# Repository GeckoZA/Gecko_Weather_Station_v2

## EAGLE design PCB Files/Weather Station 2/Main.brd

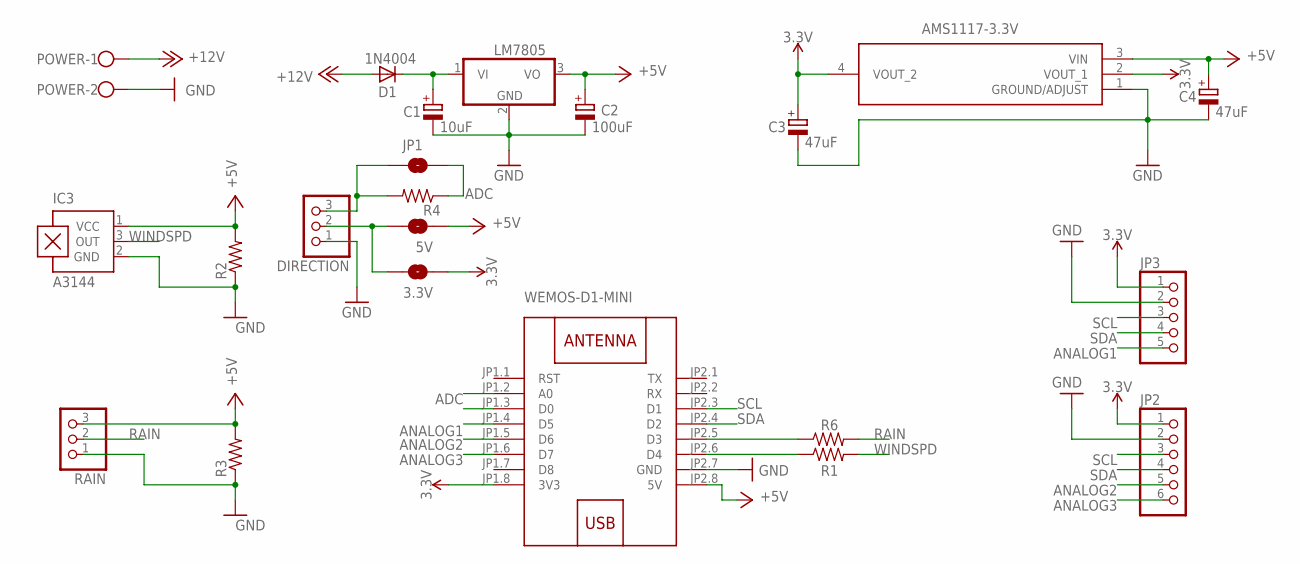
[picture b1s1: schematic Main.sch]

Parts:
3.3V, 5V: JUMPER-SMT_2_NO_NO-SILK; SMT-JUMPER_2_NO_NO-SILK
C1: 10uF; E2,5-5
C2: 100uF; E2,5-5
C3, C4: 47uF; E2,5-5
D1: 1N4004; DO41-10
DIRECTION: PINHD-1X3/90; 1X03/90
IC1: LM7805; TO220H
IC2: AMS1117-3.3V; SOT229P700X180-4N
IC3: A3144; SIP3-UA
JP1: JUMPER-SMT_2_NO_NO-SILK; SMT-JUMPER_2_NO_NO-SILK
JP2: PINHD-1X6/90; 1X06/90
JP3: PINHD-1X5/90; 1X05/90
POWER: W237-102
R1, R2, R3, R4, R6: R-US_0207/10; 0207/10
RAIN: PINHD-1X3/90; 1X03/90
U$1: WEMOS-D1-MINI

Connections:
3.3V: 3.3V.1, C3.+, IC2.2 (VOUT_1), IC2.4 (VOUT_2), JP2.1, JP3.1, U$1.JP1.8 (3V3)
+5V: 5V.1, C2.+, C4.+, IC1.3 (VO), IC2.3 (VIN), IC3.1 (VCC), R2.2, R3.2, RAIN.3, U$1.JP2.8 (5V)
+12V: D1.A, POWER.1
ADC: JP1.2, R4.1, U$1.JP1.2 (A0)
ANALOG1: JP3.5, U$1.JP1.4 (D5)
ANALOG2: JP2.5, U$1.JP1.5 (D6)
ANALOG3: JP2.6, U$1.JP1.6 (D7)
GND: C1.-, C2.-, C3.-, C4.-, DIRECTION.1, IC1.2 (GND), IC2.1 (GROUND/ADJUST), IC3.2 (GND), JP2.2, JP3.2, POWER.2, R2.1, R3.1, RAIN.1, U$1.JP2.7 (GND)
unnamed: C1.+, D1.C, IC1.1 (VI)
unnamed: R1.1, U$1.JP2.6 (D4)
unnamed: R6.1, U$1.JP2.5 (D3)
unnamed: DIRECTION.3, JP1.1, R4.2
unnamed: 3.3V.2, 5V.2, DIRECTION.2
RAIN: R6.2, RAIN.2
SCL: JP2.3, JP3.3, U$1.JP2.3 (D1)
SDA: JP2.4, JP3.4, U$1.JP2.4 (D2)
WINDSPD: IC3.3 (OUT), R1.2

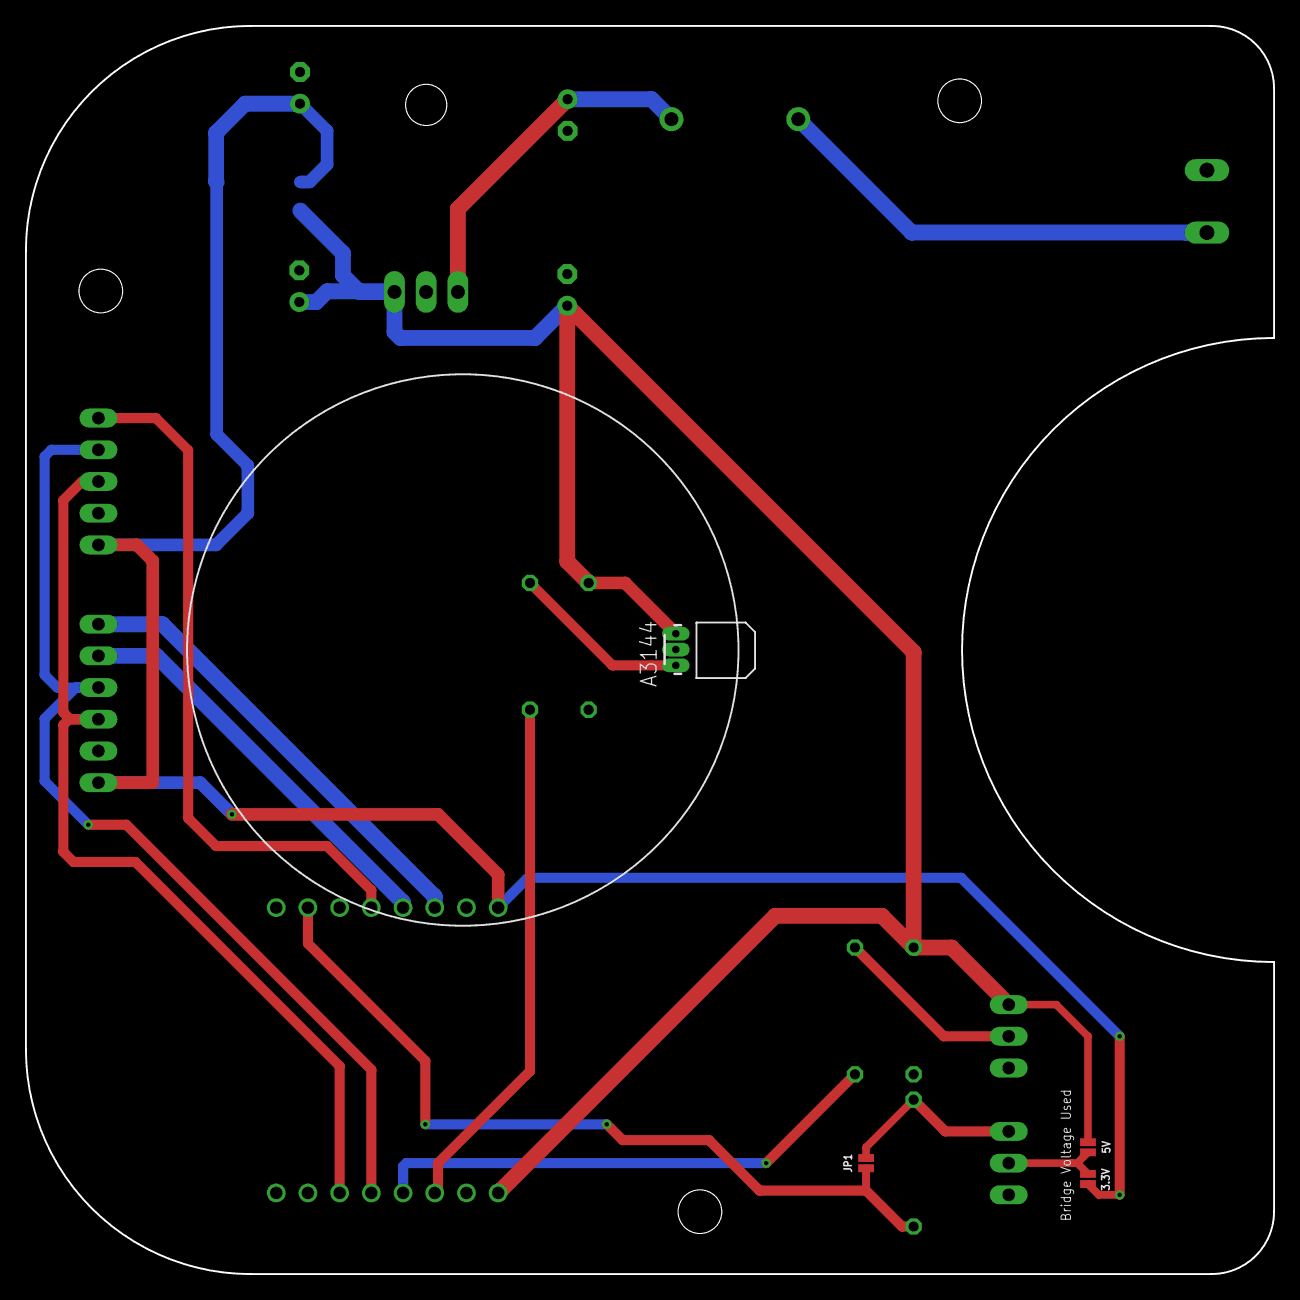
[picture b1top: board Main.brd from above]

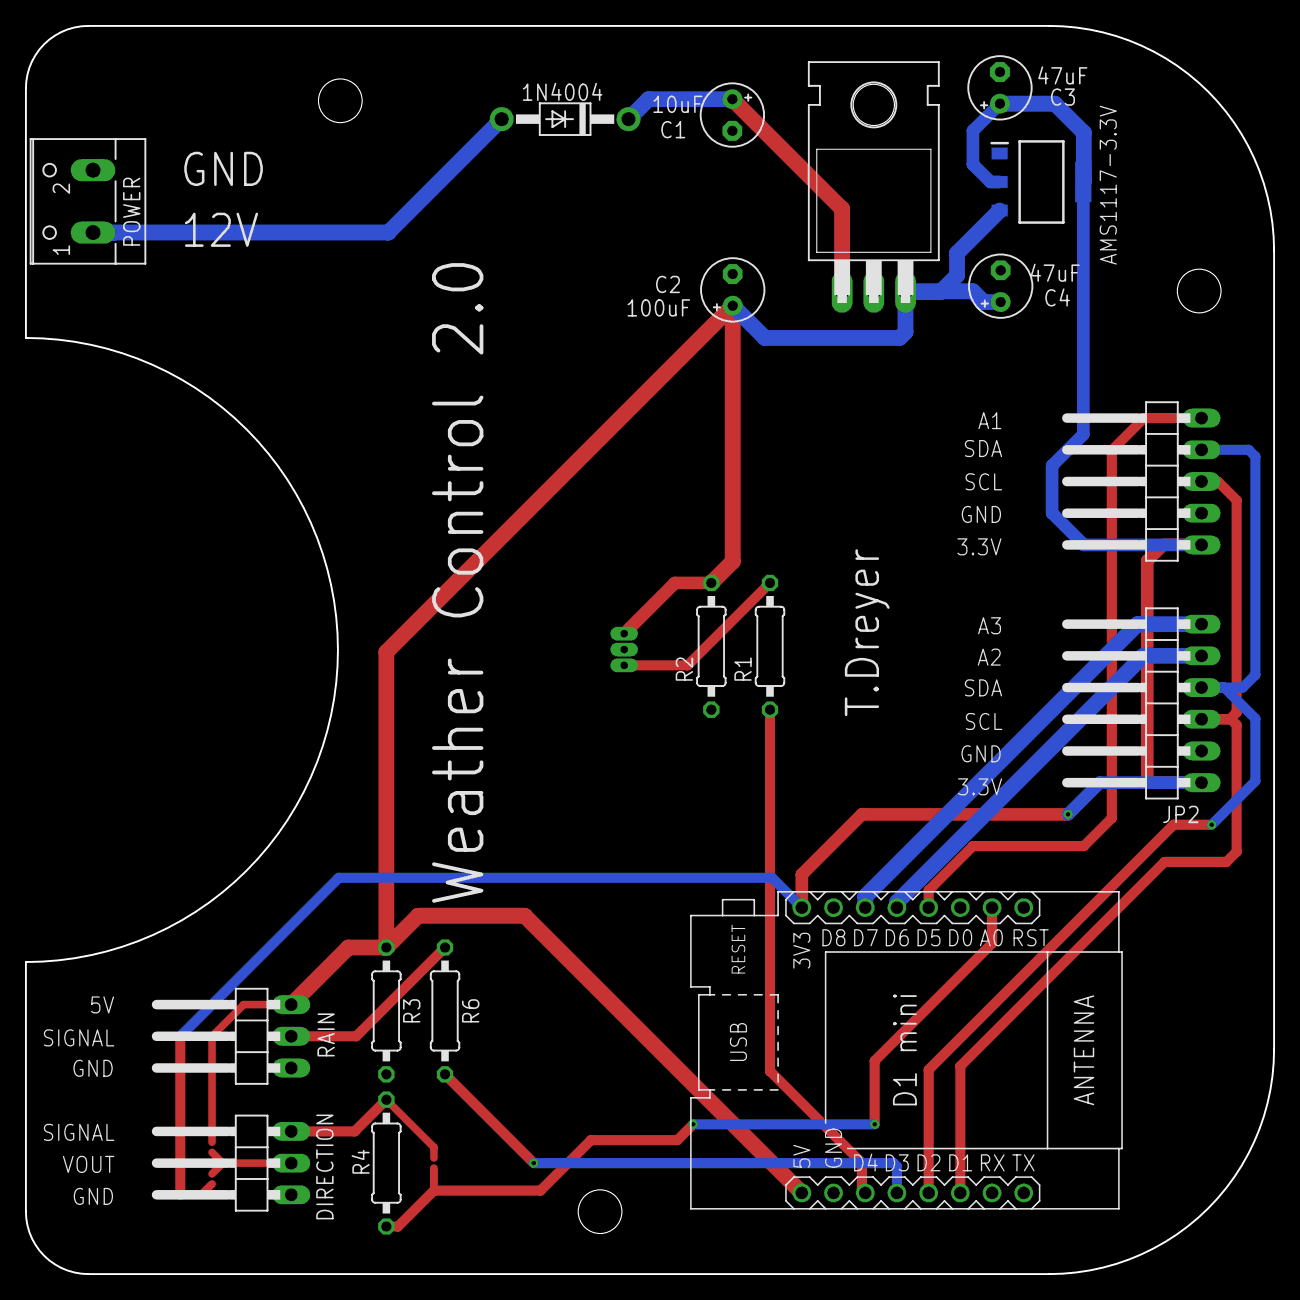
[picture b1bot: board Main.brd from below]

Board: 2 copper layers, 100.0 x 100.0 mm, 22 parts (18 on the bottom side), 17 nets.

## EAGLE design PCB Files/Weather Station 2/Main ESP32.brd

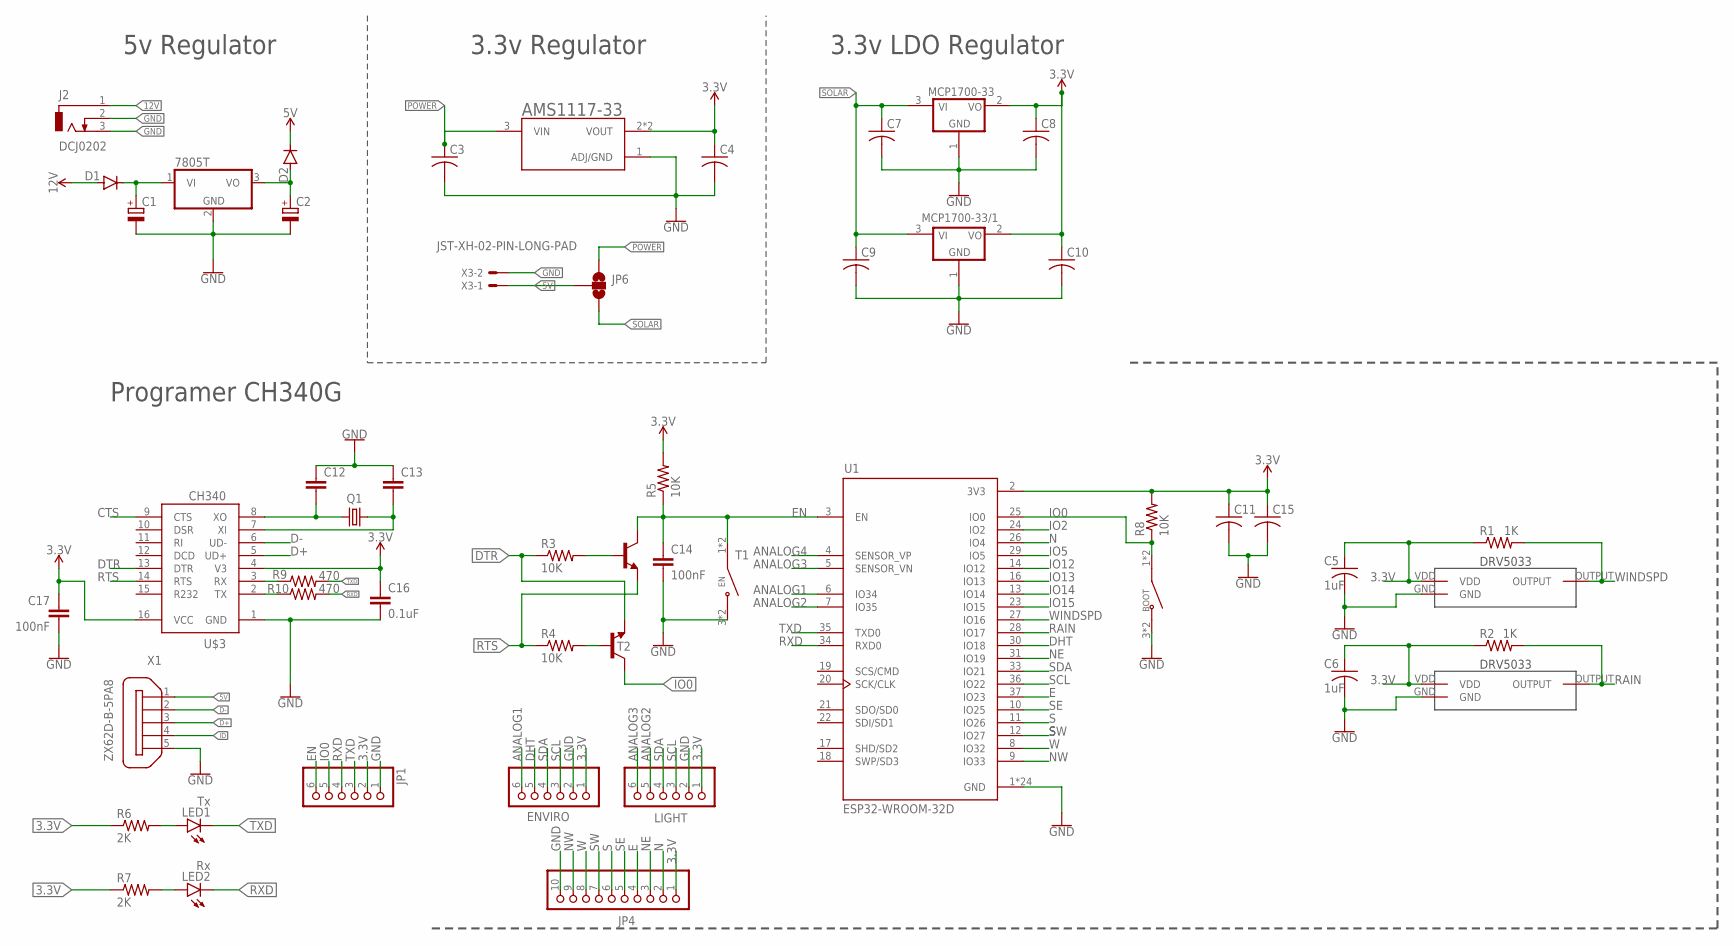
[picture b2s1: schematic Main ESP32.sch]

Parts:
AMS1117-33: AMS1117-5.0; SOT229P700X180-4N
BOOT: 2-1437565-9; SW_2-1437565-9
C1, C2: CPOL-EUE2.5-5; E2,5-5
C3, C4, C7, C8, C9, C10, C11, C15: C-USC1206K; C1206K
C5, C6: 1uF; C1206K
C12, C13: C-EUC1206K; C1206K
C14, C17: 100nF; C1206K
C16: 0.1uF; C1206K
D1, D2: 1N4148DO35-10; DO35-10
EN: 2-1437565-9; SW_2-1437565-9
ENVIRO: PINHD-1X6/90; 1X06/90
IC1: 7805T; TO220H
J2: DCJ0202
JP1: PINHD-1X6; 1X06
JP4: PINHD-1X10/90; 1X10/90
JP6: JUMPER-SMT_3_NO_SILK; SMT-JUMPER_3_NO_SILK
LED1: Tx; CHIPLED_1206
LED2: Rx; CHIPLED_1206
LIGHT: Light; 1X06/90
MCP1700-33, MCP1700-33/1: MCP1703-3302E/CB; SOT23A_MICROCHIP_CB
Q1: CRYSTALHC49S; HC49/S
R1, R2: 1K; R1206
R3, R4, R5, R8: 10K; R1206
R6, R7: 2K; R1206
R9, R10: 470; R1206
T1, T2: BC847; SOT23
U1: ESP32-WROOM-32D; MODULE_ESP32-WROOM-32D
U$1, U$2: DRV5033
U$3: CH340; SOIC16
X1: ZX62D-B-5PA8
X3: JST-XH-02-PIN-LONG-PAD; JST-XH-02-PACKAGE-LONG-PAD

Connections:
3.3V: AMS1117-33.2 (VOUT), AMS1117-33.4 (VOUT), C4.1, C5.1, C6.1, C8.1, C10.1, C11.1, C15.1, C16.1, C17.1, ENVIRO.1, JP1.2, JP4.1, LIGHT.1, MCP1700-33.2 (VO), MCP1700-33/1.2 (VO), R1.1, R2.1, R5.2, R6.1, R7.1, R8.2, U1.2 (3V3), U$1.VDD, U$2.VDD, U$3.4 (V3), U$3.16 (VCC)
5V: D2.C, JP6.2, X1.1, X3.1
12V: D1.A, J2.1
ANALOG1: ENVIRO.6, U1.6 (IO34)
ANALOG2: LIGHT.5, U1.7 (IO35)
ANALOG3: LIGHT.6, U1.5 (SENSOR_VN)
ANALOG4: U1.4 (SENSOR_VP)
CTS: U$3.9 (CTS)
D+: U$3.5 (UD+), X1.3
D-: U$3.6 (UD-), X1.2
DHT: ENVIRO.5, U1.30 (IO18)
DTR: R3.1, T2.2 (E), U$3.13 (DTR)
E: JP4.4, U1.37 (IO23)
EN: C14.1, EN.1 (COM), EN.2 (COM), JP1.6, R5.1, T1.3 (C), U1.3 (EN)
GND: AMS1117-33.1 (ADJ/GND), BOOT.3 (NO), BOOT.4 (NO), C1.-, C2.-, C3.2, C4.2, C5.2, C6.2, C7.2, C8.2, C9.2, C10.2, C11.2, C12.1, C13.1, C14.2, C15.2, C16.2, C17.2, EN.3 (NO), EN.4 (NO), ENVIRO.2, IC1.2 (GND), J2.2, J2.3, JP1.1, JP4.10, LIGHT.2, MCP1700-33.1 (GND), MCP1700-33/1.1 (GND), U1.1 (GND), U1.15 (GND), U1.38 (GND), U1.39_1 (GND), U1.39_2 (GND), U1.39_3 (GND), U1.39_4 (GND), U1.39_5 (GND), U1.39_6 (GND), U1.39_7 (GND), U1.39_8 (GND), U1.39_9 (GND), U1.39_10 (GND), U1.39_11 (GND), U1.39_12 (GND), U1.39_13 (GND), U1.39_14 (GND), U1.39_15 (GND), U1.39_16 (GND), U1.39_17 (GND), U1.39_18 (GND), U1.39_19 (GND), U1.39_20 (GND), U1.39_21 (GND), U$1.GND, U$2.GND, U$3.1 (GND), X1.5, X3.2
ID: X1.4
IO0: BOOT.1 (COM), BOOT.2 (COM), JP1.5, R8.1, T2.3 (C), U1.25 (IO0)
IO2: U1.24 (IO2)
IO5: U1.29 (IO5)
IO12: U1.14 (IO12)
IO13: U1.16 (IO13)
IO14: U1.13 (IO14)
IO15: U1.23 (IO15)
N: JP4.2, U1.26 (IO4)
unnamed: C1.+, D1.C, IC1.1 (VI)
unnamed: C2.+, D2.A, IC1.3 (VO)
unnamed: C12.2, Q1.2, U$3.8 (XO)
unnamed: C13.2, Q1.1, U$3.7 (XI)
unnamed: LED1.A, R6.2
unnamed: LED2.A, R7.2
unnamed: R9.1, U$3.3 (RX)
unnamed: R3.2, T1.1 (B)
unnamed: R10.1, U$3.2 (TX)
unnamed: R4.2, T2.1 (B)
NE: JP4.3, U1.31 (IO19)
NW: JP4.9, U1.9 (IO33)
POWER: AMS1117-33.3 (VIN), C3.1, JP6.1
RAIN: R2.2, U1.28 (IO17), U$1.OUTPUT
RTS: R4.1, T1.2 (E), U$3.14 (RTS)
RXD: JP1.4, LED2.C, R10.2, U1.34 (RXD0)
S: JP4.6, U1.11 (IO26)
SCL: ENVIRO.3, LIGHT.3, U1.36 (IO22)
SDA: ENVIRO.4, LIGHT.4, U1.33 (IO21)
SE: JP4.5, U1.10 (IO25)
SOLAR: C7.1, C9.1, JP6.3, MCP1700-33.3 (VI), MCP1700-33/1.3 (VI)
SW: JP4.7, U1.12 (IO27)
TXD: JP1.3, LED1.C, R9.2, U1.35 (TXD0)
W: JP4.8, U1.8 (IO32)
WINDSPD: R1.2, U1.27 (IO16), U$2.OUTPUT

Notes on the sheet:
3.3v Regulator
5v Regulator
3.3v LDO Regulator
Programer CH340G

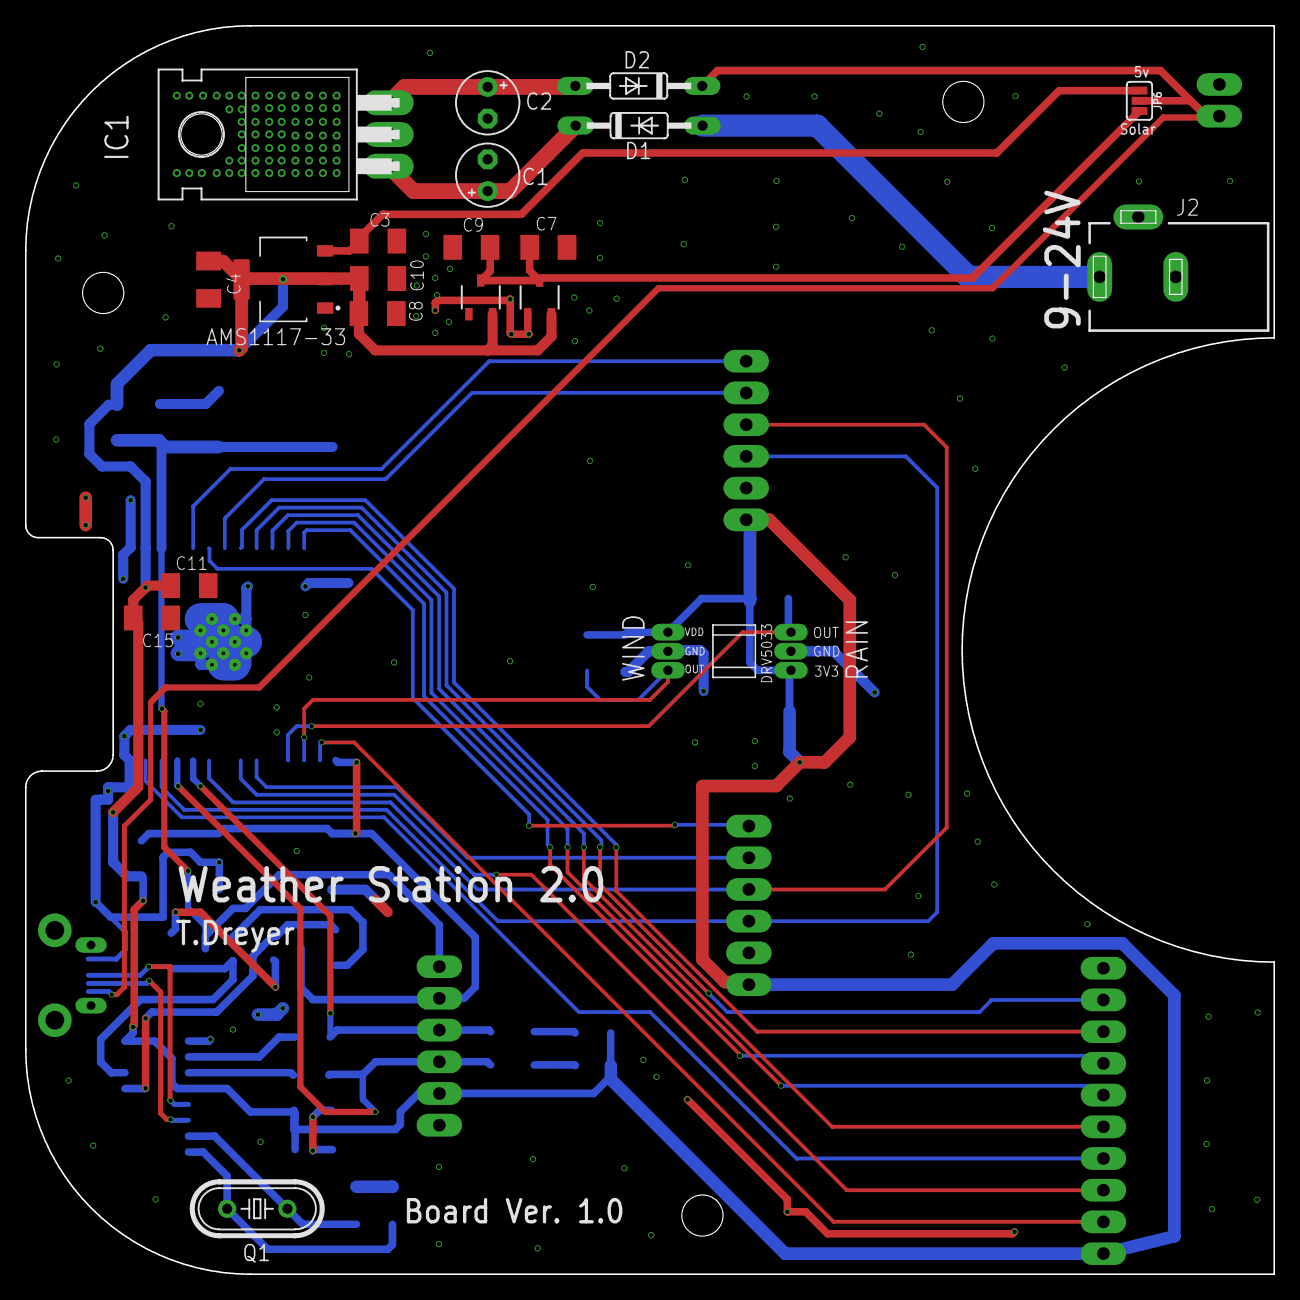
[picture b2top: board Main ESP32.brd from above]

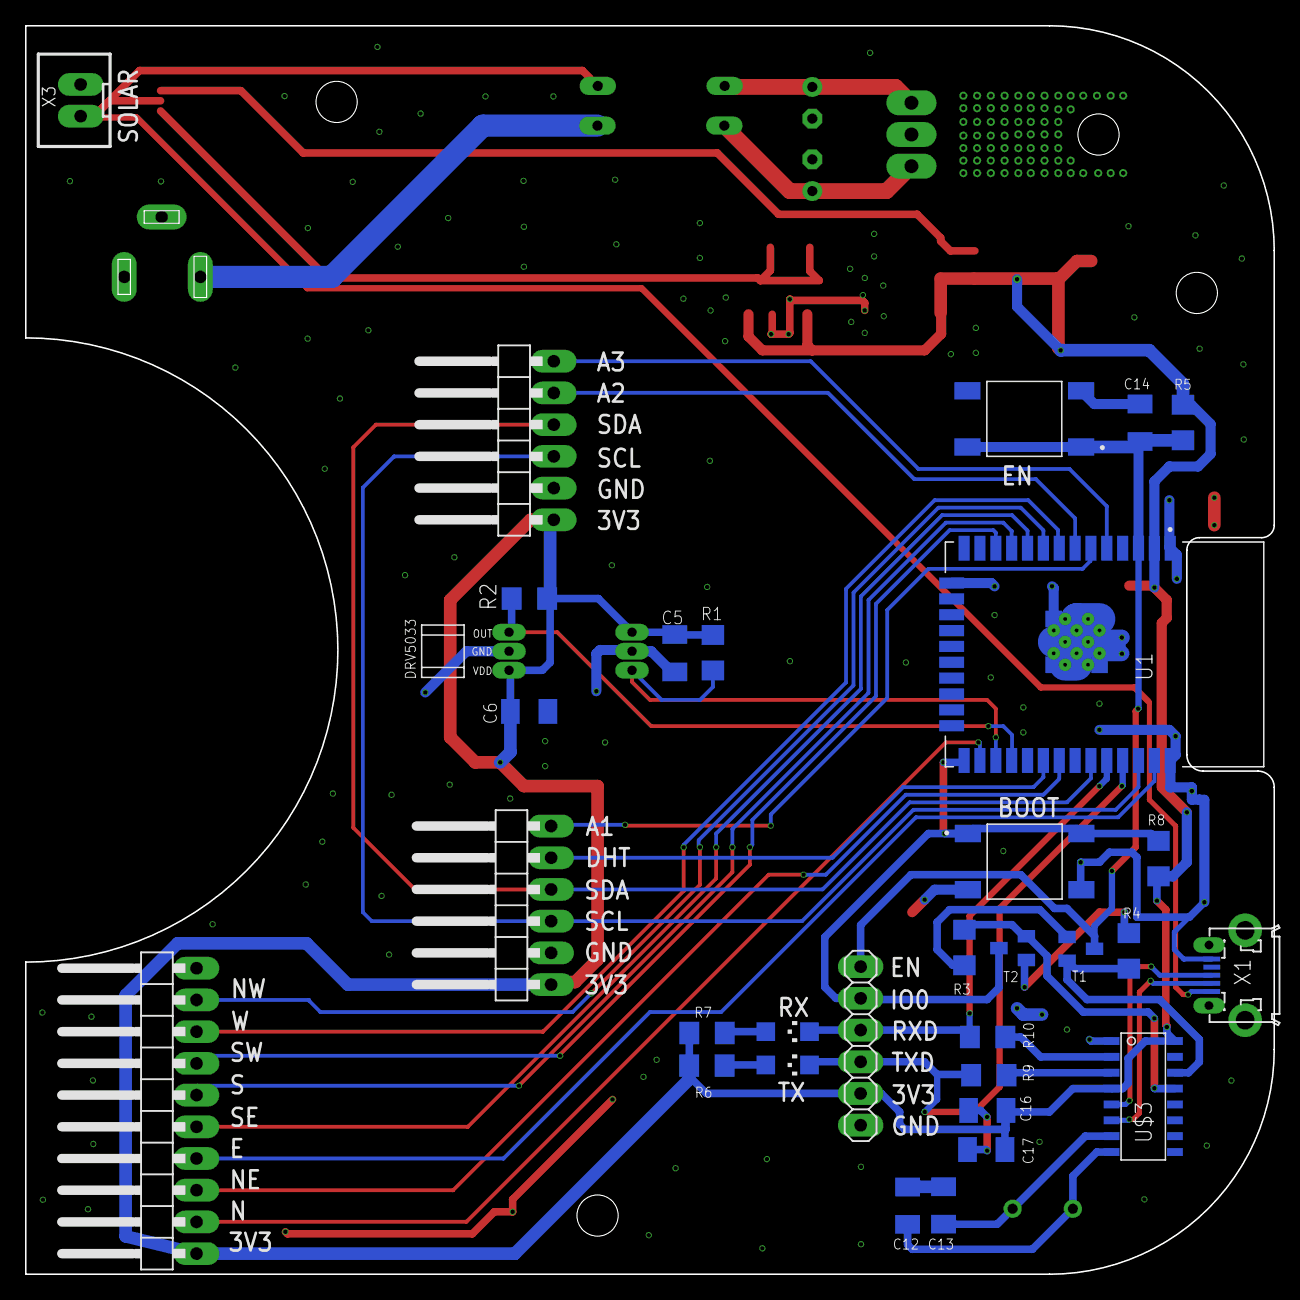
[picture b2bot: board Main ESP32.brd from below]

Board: 2 copper layers, 100.0 x 100.0 mm, 52 parts (32 on the bottom side), 40 nets.

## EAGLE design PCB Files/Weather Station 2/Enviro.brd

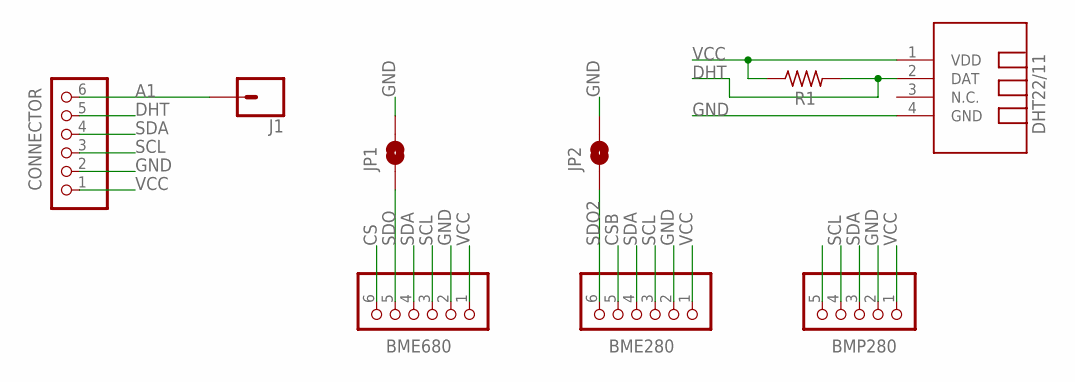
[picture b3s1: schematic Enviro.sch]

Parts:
BME280, BME680: PINHD-1X6; 1X06
BMP280: PINHD-1X5; 1X05
CONNECTOR: PINHD-1X6; 1X06
J1: CONN_01PTH_LONGPAD; 1X01_LONGPAD
JP1, JP2: JUMPER-SMT_2_NO_SILK; SMT-JUMPER_2_NO_SILK
R1: R-US_R1206; R1206
U$1: DHT22/11; TEMP-HUM-SENSOR-DHT22

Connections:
A1: CONNECTOR.6, J1.1
CS: BME680.6
CSB: BME280.5
DHT: CONNECTOR.5, R1.2, U$1.2 (DAT)
GND: BME280.2, BME680.2, BMP280.2, CONNECTOR.2, JP1.2, JP2.2, U$1.4 (GND)
SCL: BME280.3, BME680.3, BMP280.4, CONNECTOR.3
SDA: BME280.4, BME680.4, BMP280.3, CONNECTOR.4
SDO: BME680.5, JP1.1
SDO2: BME280.6, JP2.1
VCC: BME280.1, BME680.1, BMP280.1, CONNECTOR.1, R1.1, U$1.1 (VDD)

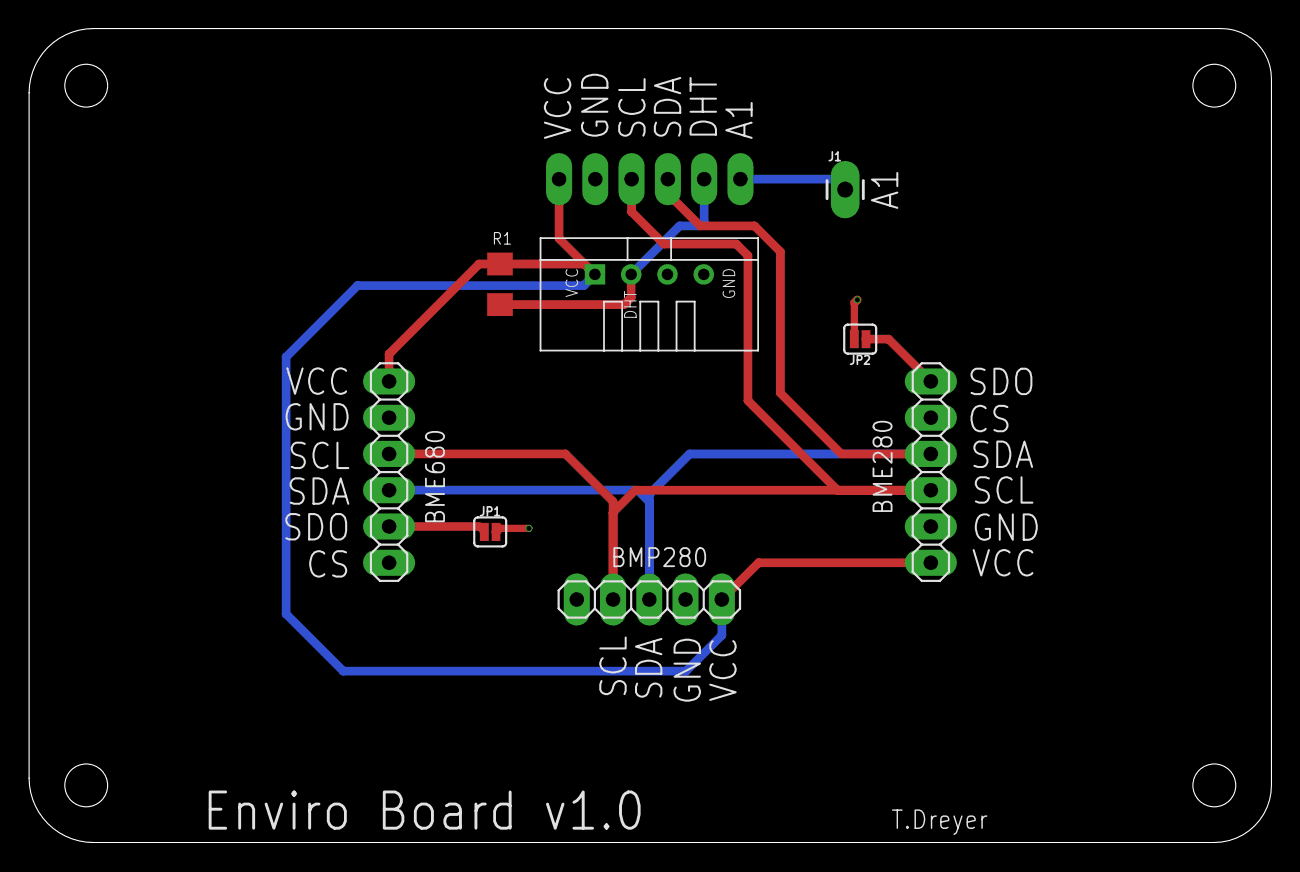
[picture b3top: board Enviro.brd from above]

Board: 2 copper layers, 87.0 x 57.0 mm, 9 parts (1 on the bottom side), 8 nets.

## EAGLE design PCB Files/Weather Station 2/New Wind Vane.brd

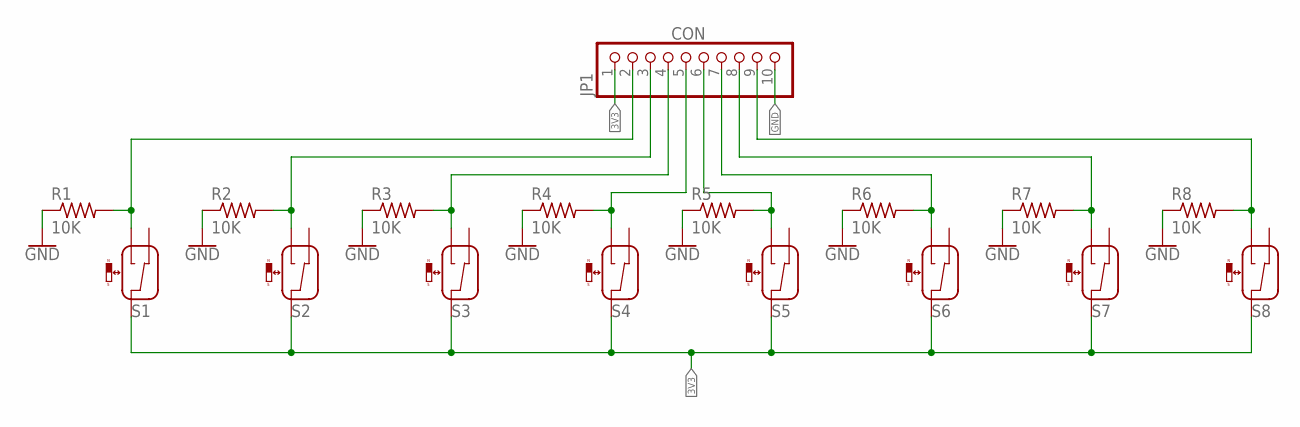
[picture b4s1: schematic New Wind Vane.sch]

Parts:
JP1: CON; 1X10/90
R1, R2, R3, R4, R5, R6, R7, R8: 10K; R1206
S1, S2, S3, S4, S5, S6, S7, S8: REED-SWITCH-NO-NC; MK6-8-C

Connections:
3V3: JP1.1, S1.COM, S2.COM, S3.COM, S4.COM, S5.COM, S6.COM, S7.COM, S8.COM
GND: JP1.10, R1.1, R2.1, R3.1, R4.1, R5.1, R6.1, R7.1, R8.1
unnamed: JP1.2, R1.2, S1.NO
unnamed: JP1.3, R2.2, S2.NO
unnamed: JP1.4, R3.2, S3.NO
unnamed: JP1.5, R4.2, S4.NO
unnamed: JP1.6, R5.2, S5.NO
unnamed: JP1.7, R6.2, S6.NO
unnamed: JP1.8, R7.2, S7.NO
unnamed: JP1.9, R8.2, S8.NO

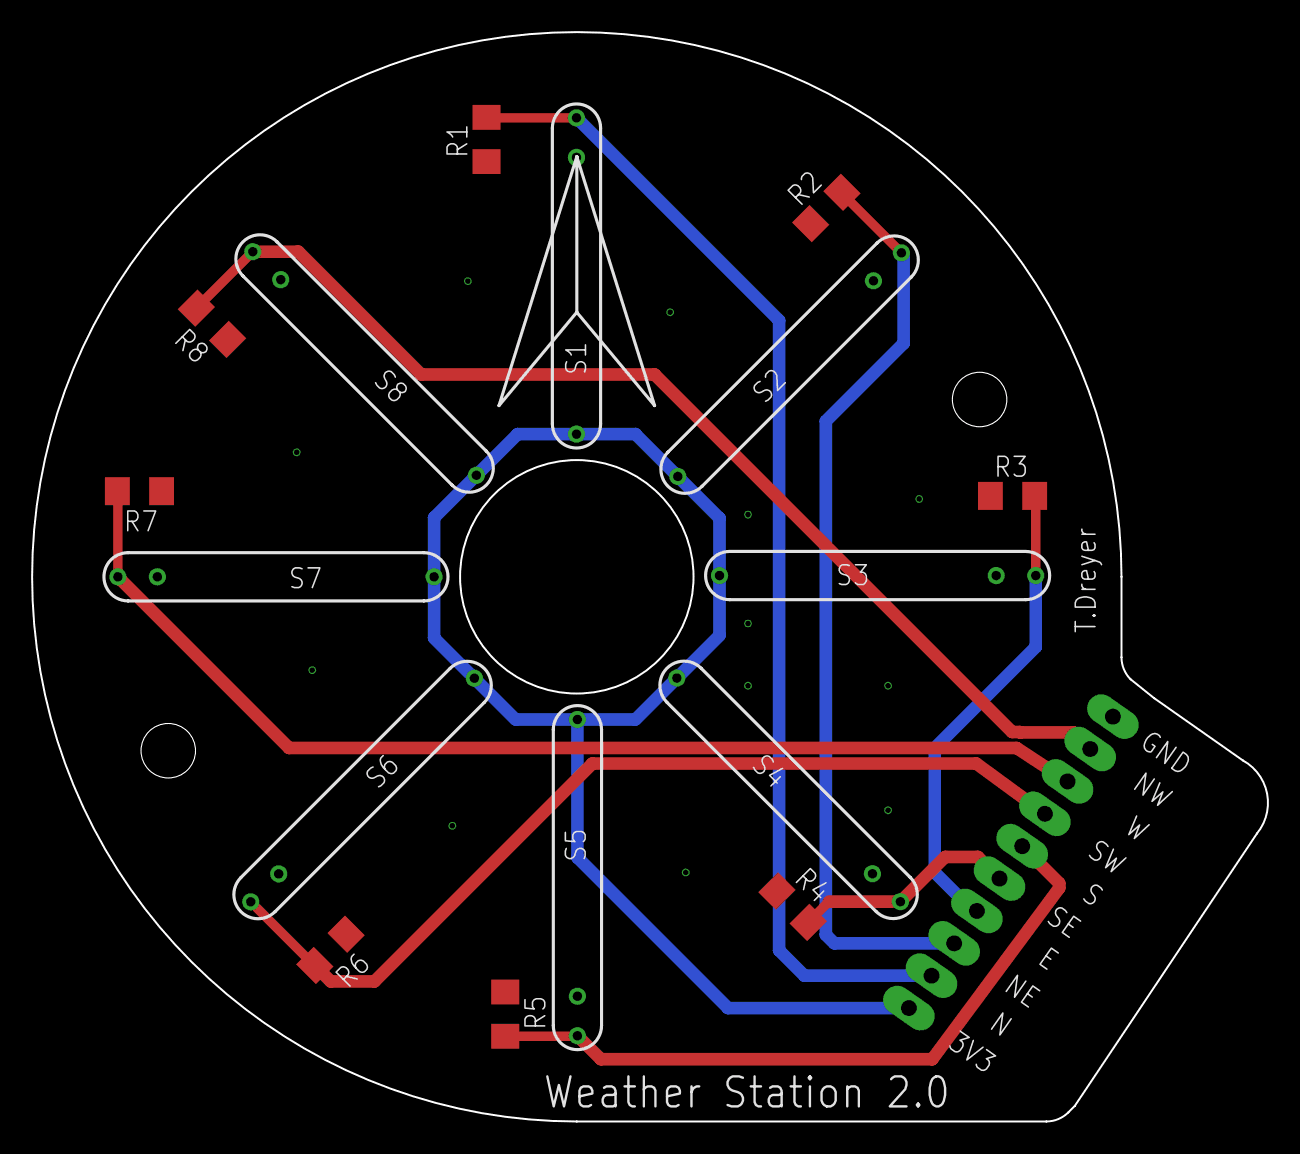
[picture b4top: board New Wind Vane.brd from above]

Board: 2 copper layers, 79.4 x 70.0 mm, 17 parts (1 on the bottom side), 10 nets.

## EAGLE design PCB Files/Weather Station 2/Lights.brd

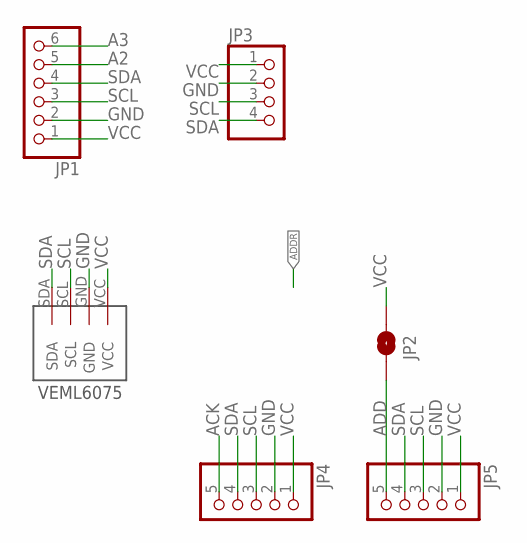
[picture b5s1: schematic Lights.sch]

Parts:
JP1: PINHD-1X6; 1X06
JP2: JUMPER-SMT_2_NO_SILK; SMT-JUMPER_2_NO_SILK
JP3: PINHD-1X4; 1X04
JP4, JP5: PINHD-1X5; 1X05
U$2: VEML6075

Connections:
A2: JP1.5
A3: JP1.6
ACK: JP4.5
ADD: JP2.1, JP5.5
GND: JP1.2, JP3.2, JP4.2, JP5.2, U$2.GND
SCL: JP1.3, JP3.3, JP4.3, JP5.3, U$2.SCL
SDA: JP1.4, JP3.4, JP4.4, JP5.4, U$2.SDA
VCC: JP1.1, JP2.2, JP3.1, JP4.1, JP5.1, U$2.VCC

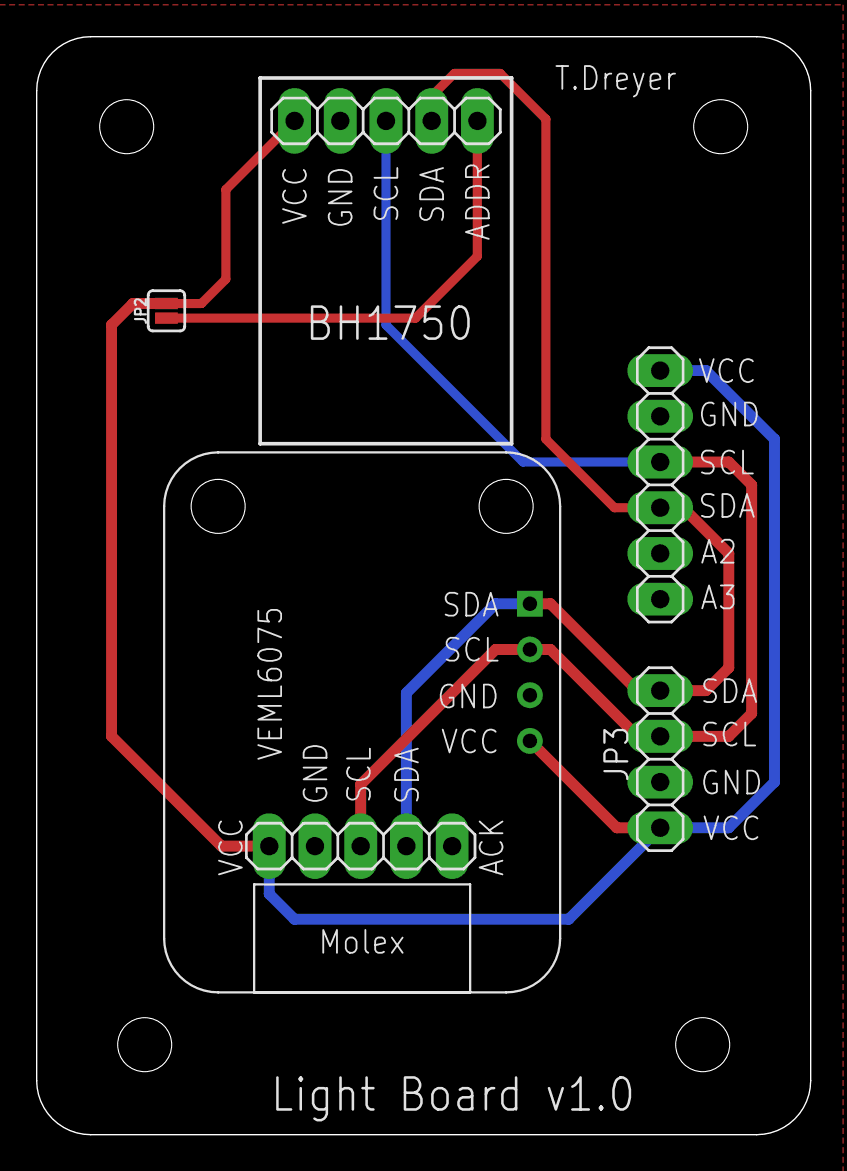
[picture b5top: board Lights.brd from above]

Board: 2 copper layers, 43.0 x 61.0 mm, 6 parts (0 on the bottom side), 5 nets.

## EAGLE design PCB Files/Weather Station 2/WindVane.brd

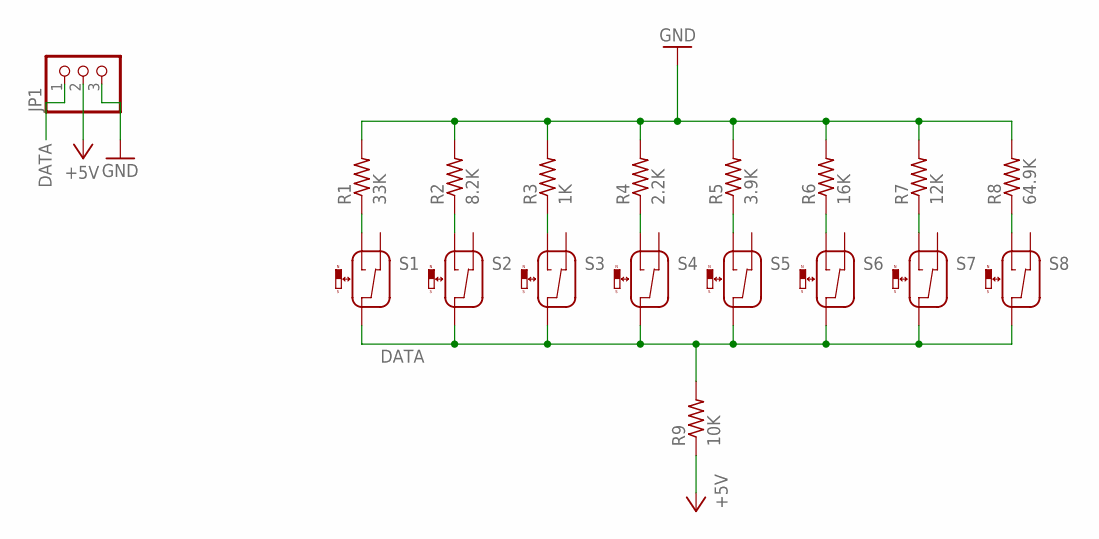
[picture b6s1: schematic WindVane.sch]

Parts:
JP1: PINHD-1X3/90; 1X03/90
R1: 33K; 0207/10
R2: 8.2K; 0207/10
R3: 1K; 0207/10
R4: 2.2K; 0207/10
R5: 3.9K; 0207/10
R6: 16K; 0207/10
R7: 12K; 0207/10
R8: 64.9K; 0207/10
R9: 10K; 0207/10
S1, S2, S3, S4, S5, S6, S7, S8: REED-SWITCH-NO-NC; MK6-8-C

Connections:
+5V: JP1.2, R9.1
DATA: JP1.1, R9.2, S1.COM, S2.COM, S3.COM, S4.COM, S5.COM, S6.COM, S7.COM, S8.COM
GND: JP1.3, R1.2, R2.2, R3.2, R4.2, R5.2, R6.2, R7.2, R8.2
unnamed: R1.1, S1.NO
unnamed: R2.1, S2.NO
unnamed: R3.1, S3.NO
unnamed: R4.1, S4.NO
unnamed: R5.1, S5.NO
unnamed: R6.1, S6.NO
unnamed: R7.1, S7.NO
unnamed: R8.1, S8.NO

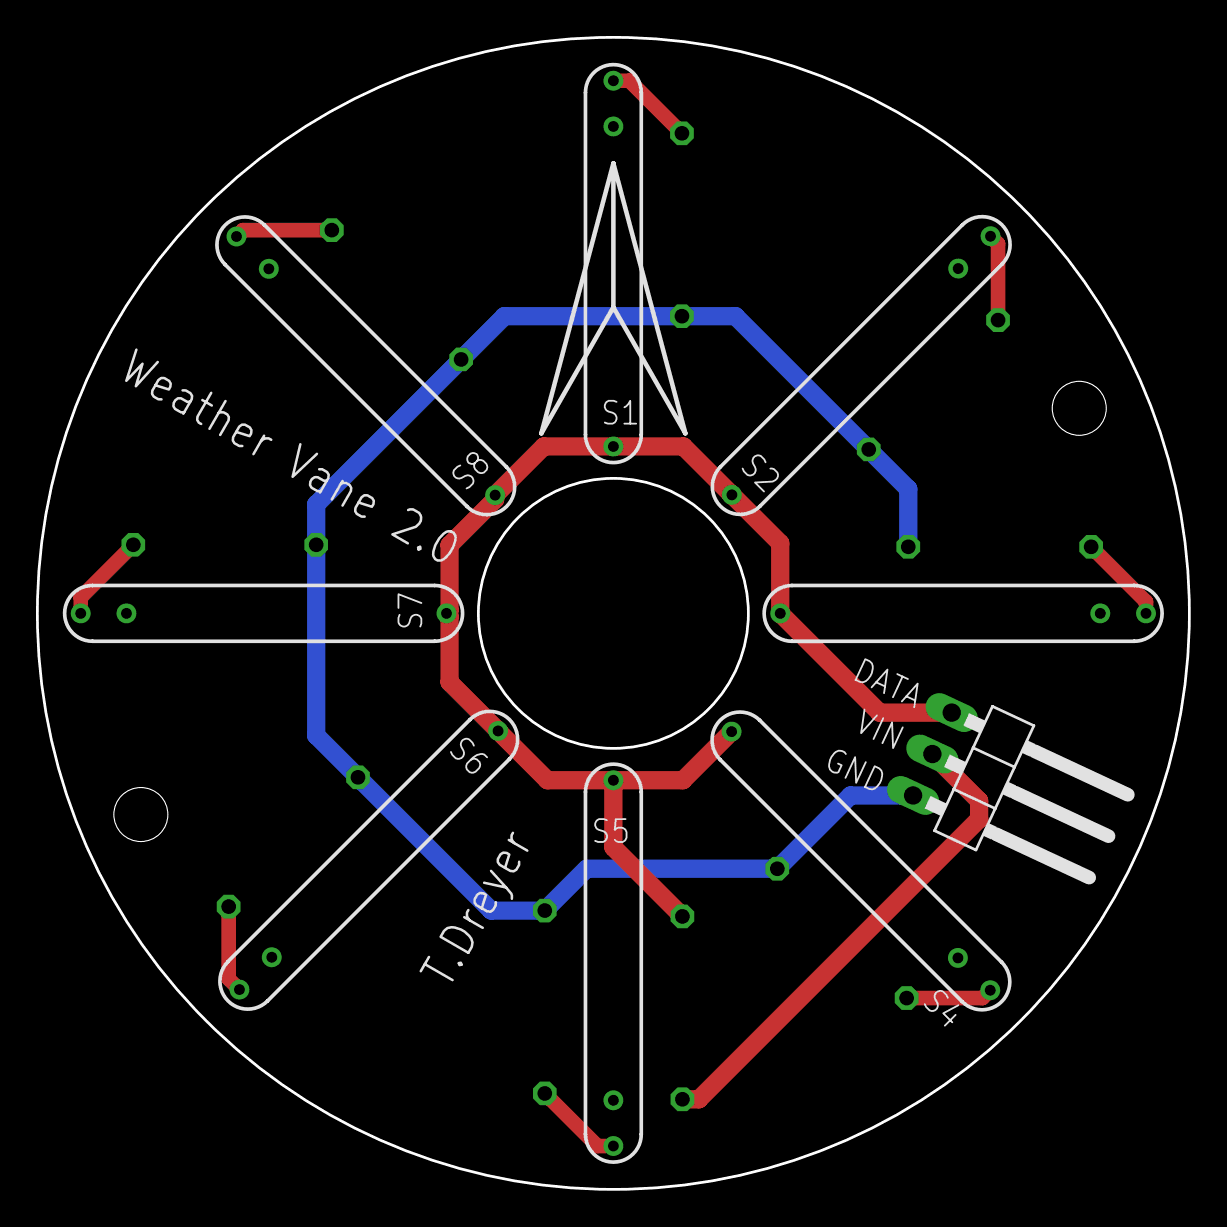
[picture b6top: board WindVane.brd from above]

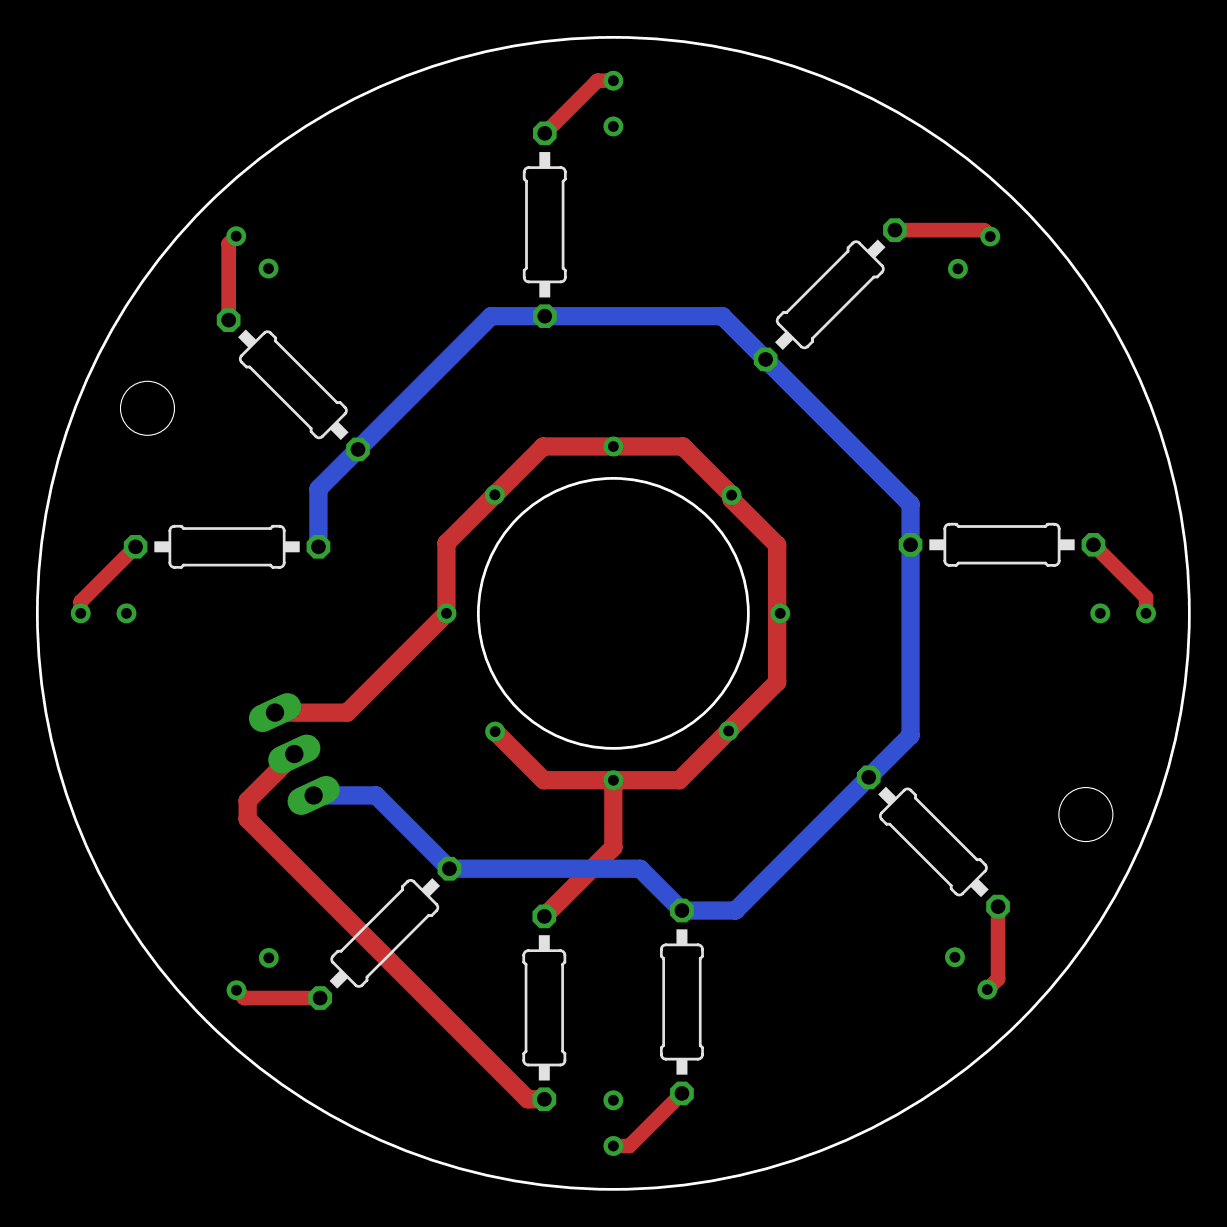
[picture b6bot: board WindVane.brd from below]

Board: 2 copper layers, 64.0 x 64.0 mm, 18 parts (9 on the bottom side), 11 nets.

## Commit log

2022-08-22 PCB and CAD
    added PCB and CAD files
2022-08-22 Update Configuration.h
    place holders

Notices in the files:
parts and their libraries:
diy-modules: Released under the Creative Commons Attribution 4.0 International License: http://creativecommons.org/licenses/by/4.0
SparkFun-Jumpers: Licensing: Creative Commons ShareAlike 4.0 International - https://creativecommons.org/licenses/by-sa/4.0
